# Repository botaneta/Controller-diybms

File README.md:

# Controller-diybms
Modificación del proyecto original diyBms de Stuart Pittaway https://github.com/stuartpittaway/diyBMSv4 <br>
Se añade un divisor de tensión a la placa controladora para medir mayor voltaje de batería con el monitor de corriente integrado.<br>
Esta modificación conyeva un riesgo electrico por manejar mayores voltajes, fuera de los limites de seguridad para las personas.<br>
No se recomienda su uso, aun teniendo los conocimientos adecuados. Lo seguro y recomendable es usar un monitor de corriente externo y aislado.

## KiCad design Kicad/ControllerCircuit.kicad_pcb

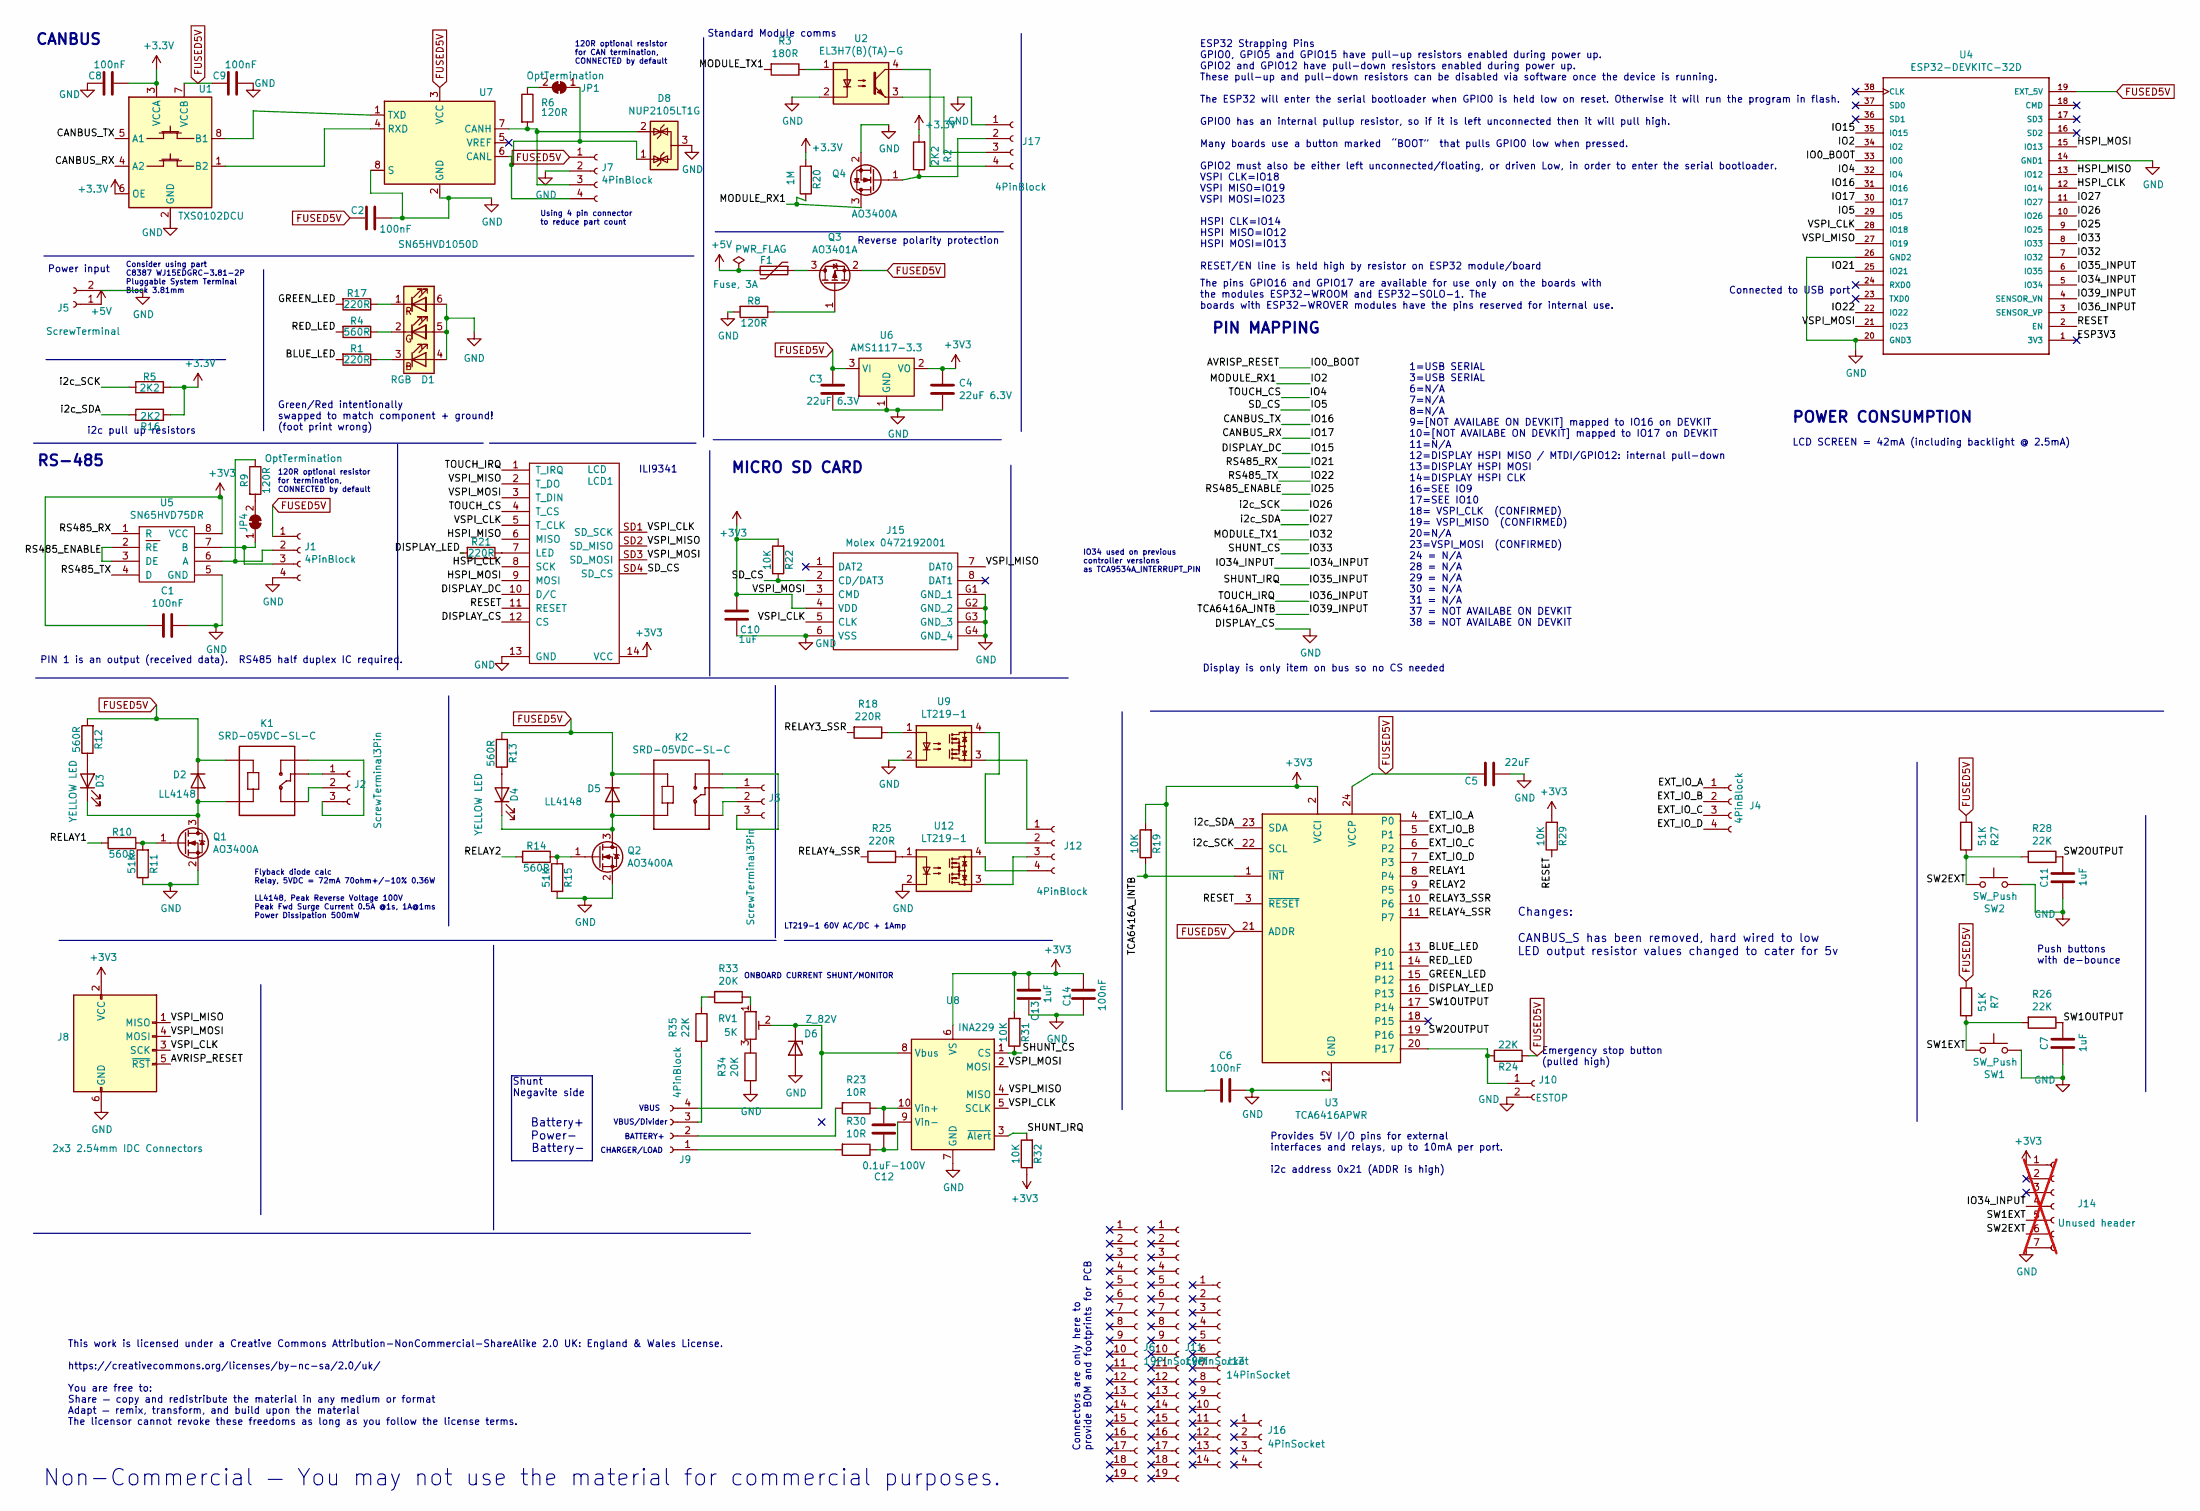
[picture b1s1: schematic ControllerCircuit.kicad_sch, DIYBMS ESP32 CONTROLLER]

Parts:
C1, C2, C6, C8, C9, C14: 100nF; C_0603_1608Metric; PartNumber CC0603KRX7R9BB104; LCSCStockCode C14663
C3, C4: 22uF 6.3V; CP_EIA-3216-18_Kemet-A_Pad1.58x1.35mm_HandSolder; PartNumber TC212A226K006Y; LCSCStockCode C110786
C5: 22uF; C_1206_3216Metric; PartNumber CL31A226KPHNNNE; LCSCStockCode C5672
C7, C10, C11, C13: 1uF; C_0603_1608Metric; PartNumber CL10A105KB8NNNC; LCSCStockCode C15849
C12: 0.1uF-100V; C_0805_2012Metric; PartNumber C0805C104K1RECAUTO; LCSCStockCode C696367
D1: RGB; LED_RGB_5050-6; LCSCStockCode C219409
D2, D5: LL4148; D_MiniMELF; PartNumber LL4148; LCSCStockCode C181117
D3, D4: YELLOW LED; LED_0603_1608Metric_Pad1.05x0.95mm_HandSolder; LCSCStockCode C72038
D6: Z_82V; D_SMA; LCSCStockCode C700490
D8: NUP2105LT1G; SOT-23; LCSCStockCode C2976509
F1: Fuse, 3A; Fuse_2920_7451Metric; PartNumber TLC-LSMD300D/16; LCSCStockCode C426964
J1, J4, J7, J9, J12, J17: 4PinBlock; WJ15EDGRC-3.81-4P; LCSCStockCode C7245
J2, J3: ScrewTerminal3Pin; Terminal-Block_5.0mm_3P-LCSC_C395850; LCSCStockCode C395850
J5: ScrewTerminal; WJ15EDGRC-3.81-2P; Manufacturer_Part_Number WJ15EDGRC-3.81-2P; LCSCStockCode C8387
J6, J11: 19PinSocket; Manufacturer_Part_Number KH-2.54FH-1X19P-H8.5; LCSCStockCode C2932678
J8: 2x3 2.54mm IDC Connectors; PinHeader_2x03_P2.54mm_Vertical; LCSCStockCode C132438
J10: ESTOP; JST_PH_S2B-PH-K_1x02_P2.00mm_Horizontal; PartNumber S2B-PH-K-S-GW; LCSCStockCode C157932
J13: 14PinSocket; Manufacturer_Part_Number KH-2.54FH-1X14P-H8.5; LCSCStockCode C2905420
J14: Unused header; PinHeader_1x07_P2.54mm_Vertical; not fitted
J15: Molex 0472192001; 0472192001; Manufacturer_Part_Number 0472192001; Mouser Part Number N/A
J16: 4PinSocket; Manufacturer_Part_Number KH-2.54FH-1X4P-H8.5; LCSCStockCode C2905415
JP1: OptTermination; SolderJumper-2_P1.3mm_Bridged_Pad1.0x1.5mm
JP4: OptTermination; SolderJumper-2_P1.3mm_Bridged_RoundedPad1.0x1.5mm
K1, K2: SRD-05VDC-SL-C; RELAY_SRD-05VDC-SL-C; PartNumber SRD-05VDC-SL-C; LCSCStockCode C35449
LCD1: LCD; TFTSPI_2_8_240x320_TOUCH
Q1, Q2, Q4: AO3400A; SOT-23; PartNumber AO3400A; LCSCStockCode C344010
Q3: AO3401A; SOT-23; LCSCStockCode C15127
R1, R17, R18, R21, R25: 220R; R_0603_1608Metric; PartNumber 0603WAF2200T5E; LCSCStockCode C22962
R2, R5, R16: 2K2; R_0603_1608Metric; PartNumber 0603WAF2201T5E; LCSCStockCode C4190
R3: 180R; R_0805_2012Metric; PartNumber 0805W8F1800T5E; LCSCStockCode C25270
R4, R10, R12, R13, R14: 560R; R_0603_1608Metric; PartNumber 0603WAF5600T5E; LCSCStockCode C23204
R6, R8, R9: 120R; R_0603_1608Metric; PartNumber 0603WAF1200T5E; LCSCStockCode C22787
R7, R11, R15, R27: 51K; R_0603_1608Metric; PartNumber 0603WAF5102T5E; LCSCStockCode C23196
R19, R22, R29, R31, R32: 10K; R_0603_1608Metric; PartNumber 0603WAF1002T5E; LCSCStockCode C25804
R20: 1M; R_0603_1608Metric; PartNumber 0603WAF1004T5E; LCSCStockCode C22935
R23, R30: 10R; R_0805_2012Metric; PartNumber 0805W8F100JT5E; LCSCStockCode C17415
R24, R26, R28: 22K; R_0603_1608Metric; PartNumber 0603WAF2202T5E; LCSCStockCode C31850
R33, R34: 20K; R_1206_3216Metric; LCSCStockCode C18003
R35: 22K; R_1206_3216Metric; LCSCStockCode C102130
RV1: 5K; Potentiometer_Bourns_3296W_Vertical; LCSCStockCode C780116
SW1, SW2: SW_Push; SW_PUSH_6mm_H5mm; PartNumber XUNPU TS-1002-10026; LCSCStockCode C455101
U1: TXS0102DCU; VSSOP-8_2.3x2mm_P0.5mm; LCSCStockCode C53434
U2: EL3H7(B)(TA)-G; SOP-4_4.4x2.6mm_P1.27mm; LCSCStockCode C32565
U3: TCA6416APWR; TSSOP-24_4.4x7.8mm_P0.65mm; LCSCStockCode C130203
U4: ESP32-DEVKITC-32D; MODULE_ESP32-DEVKITC-32D
U5: SN65HVD75DR; SOIC-8_3.9x4.9mm_P1.27mm; PartNumber SN65HVD75DR; LCSCStockCode C57928
U6: AMS1117-3.3; SOT-223-3_TabPin2; PartNumber AMS1117-3.3; LCSCStockCode C6186
U7: SN65HVD1050D; SOIC-8_3.9x4.9mm_P1.27mm; LCSCStockCode C14019
U8: INA229; VSSOP-10_3x3mm_P0.5mm; PartNumber INA229AIDGSR; LCSCStockCode C2846803
U9, U12: LT219-1; SO-4_4.4x3.6mm_P2.54mm; LCSCStockCode C2691601

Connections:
+5V: F1.2, J5.1
/AVRISP_RESET: J8.5 (~RST), U4.33 (IO0)
/BLUE_LED: R1.2, U3.13 (P10)
/CANBUS_RX: U1.4 (A2), U4.30 (IO17)
/CANBUS_TX: U1.5 (A1), U4.31 (IO16)
/DISPLAY_DC: LCD1.10 (D/C), U4.35 (IO15)
/DISPLAY_LED: R21.2, U3.16 (P13)
/ESP3V3: U4.1 (3V3)
/EXT_IO_A: J4.1, U3.4 (P0)
/EXT_IO_B: J4.2, U3.5 (P1)
/EXT_IO_C: J4.3, U3.6 (P2)
/EXT_IO_D: J4.4, U3.7 (P3)
/GREEN_LED: R17.2, U3.15 (P12)
/HSPI_CLK: LCD1.8 (SCK), U4.12 (IO14)
/HSPI_MISO: LCD1.6 (MISO), U4.13 (IO12)
/HSPI_MOSI: LCD1.9 (MOSI), U4.15 (IO13)
/IO2: Q4.3 (D), R20.1, U4.34 (IO2)
/IO4: LCD1.4 (T_CS), U4.32 (IO4)
/IO5: J15.2 (CD/DAT3), LCD1.SD4 (SD_CS), R22.1, U4.29 (IO5)
/IO21: U4.25 (IO21), U5.1 (R)
/IO22: U4.22 (IO22), U5.4 (D)
/IO25: U4.9 (IO25), U5.2 (RE), U5.3 (DE)
/IO26: R5.1, U3.22 (SCL), U4.10 (IO26)
/IO27: R16.1, U3.23 (SDA), U4.11 (IO27)
/IO32: R3.2, U4.7 (IO32)
/IO33: R31.1, U4.8 (IO33), U8.1 (CS)
/IO34_INPUT: J14.4, U4.5 (IO34)
/IO35_INPUT: R32.2, U4.6 (IO35), U8.3 (~Alert)
/IO36_INPUT: LCD1.1 (T_IRQ), U4.3 (SENSOR_VP)
/IO39_INPUT: R19.1, U3.1 (~INT), U4.4 (SENSOR_VN)
/RED_LED: R4.2, U3.14 (P11)
/RELAY1: R10.2, U3.8 (P4)
/RELAY2: R14.2, U3.9 (P5)
/RELAY3_SSR: R18.2, U3.10 (P6)
/RELAY4_SSR: R25.2, U3.11 (P7)
/RESET: LCD1.11 (RESET), R29.1, U3.3 (~RESET), U4.2 (EN)
/SW1EXT: J14.5, R7.1, R26.2, SW1.1
/SW1OUTPUT: C7.1, R26.1, U3.17 (P14)
/SW2EXT: J14.6, R27.1, R28.2, SW2.1
/SW2OUTPUT: C11.1, R28.1, U3.19 (P16)
/VSPI_CLK: J8.3 (SCK), J15.5 (CLK), LCD1.5 (T_CLK), LCD1.SD1 (SD_SCK), U4.28 (IO18), U8.5 (SCLK)
/VSPI_MISO: J8.1 (MISO), J15.7 (DAT0), LCD1.2 (T_DO), LCD1.SD2 (SD_MISO), U4.27 (IO19), U8.4 (MISO)
/VSPI_MOSI: J8.4 (MOSI), J15.3 (CMD), LCD1.3 (T_DIN), LCD1.SD3 (SD_MOSI), U4.21 (IO23), U8.2 (MOSI)
FUSED5V: C2.1, C3.1, C5.2, C9.1, D2.1 (K), D5.1 (K), J1.1, J7.1, K1.A1, K2.A1, Q3.2 (S), R7.2, R12.2, R13.2, R24.2, R27.2, U1.7 (VCCB), U3.21 (ADDR), U3.24 (VCCP), U4.19 (EXT_5V), U6.3 (VI), U7.3 (VCC)
GND: C1.2, C2.2, C3.2, C4.2, C5.1, C6.2, C7.2, C8.1, C9.2, C10.2, C11.2, C13.1, C14.1, D1.4 (BA), D1.5 (GA), D1.6 (RA), D6.2 (A), D8.3 (A), J1.4, J5.2, J7.2, J8.6 (GND), J10.2, J14.7, J15.6 (VSS), J15.G1 (GND_1), J15.G2 (GND_2), J15.G3 (GND_3), J15.G4 (GND_4), J17.1, LCD1.12 (CS), LCD1.13 (GND), Q1.2 (S), Q2.2 (S), Q4.2 (S), R8.2, R11.1, R15.1, R34.2, SW1.2, SW2.2, U1.2 (GND), U2.2, U3.12 (GND), U4.14 (GND1), U4.20 (GND3), U4.26 (GND2), U5.5 (GND), U6.1 (GND), U7.2 (GND), U7.8 (S), U8.7 (GND), U9.2, U12.2
unnamed: D1.3 (BK), R1.1
unnamed: D1.2 (GK), R4.1
unnamed: D1.1 (RK), R17.1
unnamed: D2.2 (A), D3.1 (K), K1.A2, Q1.3 (D)
unnamed: D3.2 (A), R12.1
unnamed: D4.2 (A), R13.1
unnamed: D4.1 (K), D5.2 (A), K2.A2, Q2.3 (D)
unnamed: D6.1 (K), J9.4, RV1.2, U8.8 (Vbus)
unnamed: J1.2, R9.1, U5.6 (A)
unnamed: J1.3, JP4.1 (A), U5.7 (B)
unnamed: J2.1, K1.COM
unnamed: J2.2, K1.NC
unnamed: J2.3, K1.NO
unnamed: J3.1, K2.COM
unnamed: J3.2, K2.NC
unnamed: J3.3, K2.NO
unnamed: D8.2 (K), J7.3, R6.2, U7.7 (CANH)
unnamed: D8.1 (K), J7.4, JP1.1 (A), U7.6 (CANL)
unnamed: J9.1, R30.2
unnamed: J9.2, R23.2
unnamed: J9.3, R35.2
unnamed: J10.1, R24.1, U3.20 (P17)
unnamed: J12.1, U9.3
unnamed: J12.2, U9.4
unnamed: J12.3, U12.3
unnamed: J12.4, U12.4
unnamed: J17.2, Q4.1 (G), R2.1
unnamed: J17.3, U2.3
unnamed: J17.4, U2.4
unnamed: JP1.2 (B), R6.1
unnamed: JP4.2 (B), R9.2
unnamed: LCD1.7 (LED), R21.1
unnamed: Q1.1 (G), R10.1, R11.2
unnamed: Q2.1 (G), R14.1, R15.2
unnamed: F1.1, Q3.3 (D)
unnamed: Q3.1 (G), R8.1
unnamed: R3.1, U2.1
unnamed: R18.1, U9.1
unnamed: R25.1, U12.1
unnamed: R33.1, RV1.1
unnamed: R33.2, R35.1
unnamed: R34.1, RV1.3
unnamed: U1.8 (B1), U7.1 (TXD)
unnamed: U1.1 (B2), U7.4 (RXD)
unnamed: C12.1, R23.1, U8.10 (Vin+)
unnamed: C12.2, R30.1, U8.9 (Vin-)

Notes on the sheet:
Standard Module comms
ILI9341
CANBUS
Push buttons with de-bounce
Display is only item on bus so no CS needed
PIN 1 is an output (received data). RS485 half duplex IC required.
Changes: CANBUS_S has been removed, hard wired to low LED output resistor values changed to cater for 5v
Connectors are only here to provide BOM and footprints for PCB
Non-Commercial — You may not use the material for commercial purposes.
Shunt Negavite side
120R optional resistor for CAN termination, CONNECTED by default
Consider using part C8387 WJ15EDGRC-3.81-2P Pluggable System Terminal Block 3.81mm
Connected to USB port
Reverse polarity protection
PIN MAPPING
ESP32 Strapping Pins GPIO0, GPIO5 and GPIO15 have pull-up resistors enabled during power up. GPIO2 and GPIO12 have pull-down resistors enabled during power up. These pull-up and pull-down resistors can be disabled via software once the device is running. The ESP32 will enter the serial bootloader w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
VBUS/Divider
Flyback diode calc Relay, 5VDC = 72mA 70ohm+/-10% 0.36W LL4148, Peak Reverse Voltage 100V Peak Fwd Surge Current 0.5A @1s, 1A@1ms Power Dissipation 500mW
POWER CONSUMPTION
Provides 5V I/O pins for external interfaces and relays, up to 10mA per port. i2c address 0x21 (ADDR is high)
i2c pull up resistors
LCD SCREEN = 42mA (including backlight @ 2.5mA)
CHARGER/LOAD
1=USB SERIAL 3=USB SERIAL 6=N/A 7=N/A 8=N/A 9=[NOT AVAILABE ON DEVKIT] mapped to IO16 on DEVKIT 10=[NOT AVAILABE ON DEVKIT] mapped to IO17 on DEVKIT 11=N/A 12=DISPLAY HSPI MISO / MTDI/GPIO12: internal pull-down 13=DISPLAY HSPI MOSI 14=DISPLAY HSPI CLK 16=SEE IO9 17=SEE IO10 18= VSPI_CLK (CONFIRMED)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
Emergency stop button (pulled high)
This work is licensed under a Creative Commons Attribution-NonCommercial-ShareAlike 2.0 UK: England & Wales License. https://creativecommons.org/licenses/by-nc-sa/2.0/uk/ You are free to: Share — copy and redistribute the material in any medium or format Adapt — remix, transform, and build upon the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
BATTERY+
The pins GPIO16 and GPIO17 are available for use only on the boards with the modules ESP32-WROOM and ESP32-SOLO-1. The boards with ESP32-WROVER modules have the pins reserved for internal use.
Power input
Battery-
Using 4 pin connector to reduce part count
Power-
Green/Red intentionally swapped to match component + ground! (foot print wrong)
ONBOARD CURRENT SHUNT/MONITOR
RS-485
IO34 used on previous controller versions as TCA9534A_INTERRUPT_PIN
Battery+
VBUS
LT219-1 60V AC/DC + 1Amp
120R optional resistor for termination, CONNECTED by default

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
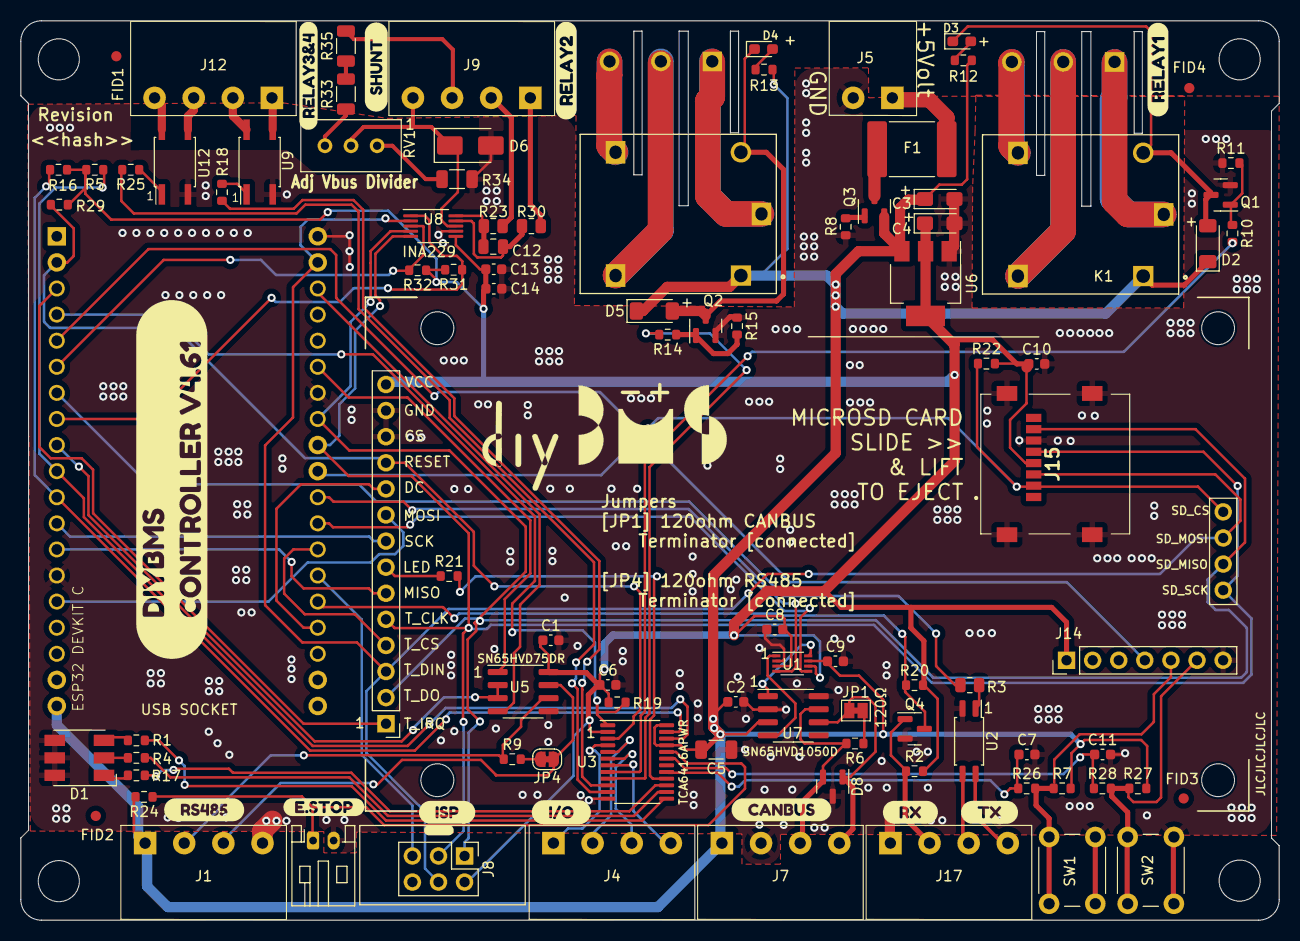
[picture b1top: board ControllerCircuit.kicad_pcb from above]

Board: 2 copper layers, 122.5 x 87.5 mm, 118 parts (1 on the bottom side), 91 nets.

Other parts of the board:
FID1, FID2, FID3, FID4: Fiducial_1mm_Mask2mm
G99: LOGO; diybms_logo_24x10mm
REF1, REF2, REF3, REF4: MountingHole_4mm
e: LOGO; logo
kibuzzard-65B91D2D: G***; kibuzzard-65B91D2D
kibuzzard-65B91D57: G***; kibuzzard-65B91D57
kibuzzard-65B91DB3: G***; kibuzzard-65B91DB3
kibuzzard-65B91E2F: G***; kibuzzard-65B91E2F
kibuzzard-65B918A7: G***; kibuzzard-65B918A7
svg2mod1, svg2mod3, svg2mod4, svg2mod5, svg2mod6, svg2mod8, svg2mod55: G***; label

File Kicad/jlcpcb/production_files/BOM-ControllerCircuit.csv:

Comment,Designator,Footprint,LCSC
22K,"R33,R34,R35",R_1206_3216Metric,C102130
22uF 6.3V,"C3,C4",CP_EIA-3216-18_Kemet-A_Pad1.58x1.35mm_HandSolder,C110786
TCA6416APWR,U3,TSSOP-24_4.4x7.8mm_P0.65mm,C130203
2x3 2.54mm IDC Connectors,J8,PinHeader_2x03_P2.54mm_Vertical,C132438
SN65HVD1050D,U7,SOIC-8_3.9x4.9mm_P1.27mm,C14019
100nF,"C1,C14,C2,C6,C8,C9",C_0603_1608Metric,C14663
AO3401A,Q3,SOT-23,C15127
ESTOP,J10,JST_PH_S2B-PH-K_1x02_P2.00mm_Horizontal,C157932
1uF,"C10,C11,C13,C7",C_0603_1608Metric,C15849
Molex 0472192001,J15,0472192001,C164170
10R,"R23,R30",R_0805_2012Metric,C17415
LL4148,"D2,D5",D_MiniMELF,C181117
RGB,D1,LED_RGB_5050-6,C219409
120R,"R6,R8,R9",R_0603_1608Metric,C22787
1M,R20,R_0603_1608Metric,C22935
220R,"R1,R17,R18,R21,R25",R_0603_1608Metric,C22962
51K,"R11,R15,R27,R7",R_0603_1608Metric,C23196
560R,"R10,R12,R13,R14,R4",R_0603_1608Metric,C23204
180R,R3,R_0805_2012Metric,C25270
10K,"R19,R22,R29,R31,R32",R_0603_1608Metric,C25804
LT219-1,"U12,U9",SO-4_4.4x3.6mm_P2.54mm,C2691601
INA229,U8,VSSOP-10_3x3mm_P0.5mm,C2846803
4PinSocket,J16,placeholder,C2905415
14PinSocket,J13,placeholder,C2905420
19PinSocket,"J11,J6",placeholder,C2932678
NUP2105LT1G,D8,SOT-23,C2976509
22K,"R24,R26,R28",R_0603_1608Metric,C31850
EL3H7(B)(TA)-G,U2,SOP-4_4.4x2.6mm_P1.27mm,C32565
AO3400A,"Q1,Q2,Q4",SOT-23,C344010
SRD-05VDC-SL-C,"K1,K2",RELAY_SRD-05VDC-SL-C,C35449
ScrewTerminal3Pin,"J2,J3",Terminal-Block_5.0mm_3P-LCSC_C395850,C395850
2K2,"R16,R2,R5",R_0603_1608Metric,C4190
"Fuse, 3A",F1,Fuse_2920_7451Metric,C426964
SW_Push,"SW1,SW2",SW_PUSH_6mm_H5mm,C455101
TXS0102DCU,U1,VSSOP-8_2.3x2mm_P0.5mm,C53434
22uF,C5,C_1206_3216Metric,C5672
SN65HVD75DR,U5,SOIC-8_3.9x4.9mm_P1.27mm,C57928
AMS1117-3.3,U6,SOT-223-3_TabPin2,C6186
0.1uF-100V,C12,C_0805_2012Metric,C696367
Z_82V,D6,D_SMA,C700490
YELLOW LED,"D3,D4",LED_0603_1608Metric_Pad1.05x0.95mm_HandSolder,C72038
4PinBlock,"J1,J12,J17,J4,J7,J9",WJ15EDGRC-3.81-4P,C7245
5K,RV1,Potentiometer_Bourns_3296W_Vertical,C780116
ScrewTerminal,J5,WJ15EDGRC-3.81-2P,C8387
ESP32-DEVKITC-32D,U4,MODULE_ESP32-DEVKITC-32D,
OptTermination,JP1,SolderJumper-2_P1.3mm_Bridged_Pad1.0x1.5mm,
OptTermination,JP4,SolderJumper-2_P1.3mm_Bridged_RoundedPad1.0x1.5mm,
LCD,LCD1,TFTSPI_2_8_240x320_TOUCH,

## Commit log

2024-07-11 Create KiCad

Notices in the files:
Kicad/ControllerCircuit.kicad_pcb:
©2019 to 2024 Stuart Pittaway
